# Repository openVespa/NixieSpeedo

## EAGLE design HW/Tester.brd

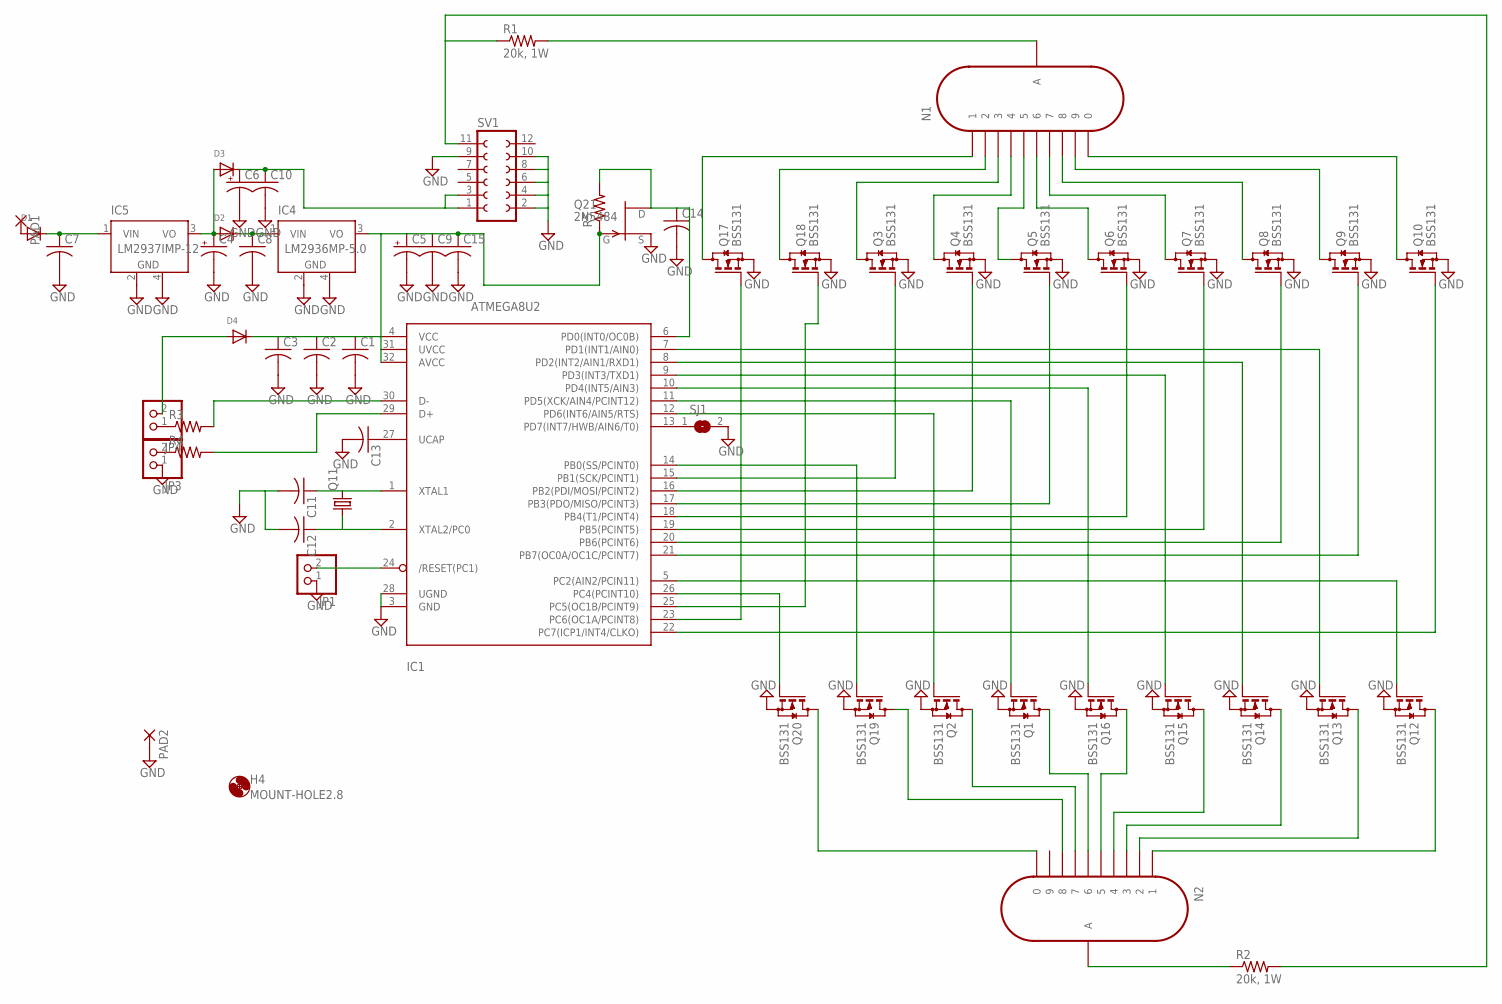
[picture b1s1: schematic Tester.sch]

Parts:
C1, C2, C3: C-USC0603K; C0603K
C4, C5, C6: CPOL-USE3.5-8; E3,5-8
C7, C8, C9, C10, C11, C12, C13, C14, C15: C-USC1206K; C1206K
D1, D2, D3: DIODESMA; SMADIODE
D4: DIODESOD-123; SOD-123
H4: MOUNT-HOLE2.8; 2,8
IC1: ATMEGA8U2; TQFP32-08
IC4: LM2936MP-5.0; SOT223
IC5: LM2937IMP-12; SOT223
JP1, JP3, JP4: PINHD-1X2; 1X02
N1, N2: IN-12A; IN-12
PAD1, PAD2: 3,81/1,4
Q1, Q2, Q3, Q4, Q5, Q6, Q7, Q8, Q9, Q10, Q12, Q13, Q14, Q15, Q16, Q17, Q18, Q19, Q20: BSS131; SOT23
Q11: CRYSTALHC49S; HC49/S
Q21: 2N5484; TO92-
R1: 20k, 1W; 0309/12
R2: 20k, 1W; 0309V
R3, R4, R5: R-US_R0805; R0805
SJ1: SJ
SV1: FE06-2

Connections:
GND: C1.2, C2.2, C3.2, C4.-, C5.-, C6.-, C7.2, C8.2, C9.2, C10.2, C11.2, C12.2, C13.2, C14.2, C15.2, IC1.3 (GND), IC1.28 (UGND), IC4.2 (GND), IC4.4 (GND), IC5.2 (GND), IC5.4 (GND), JP1.1, JP3.1, PAD2.1, Q1.2 (S), Q2.2 (S), Q3.2 (S), Q4.2 (S), Q5.2 (S), Q6.2 (S), Q7.2 (S), Q8.2 (S), Q9.2 (S), Q10.2 (S), Q12.2 (S), Q13.2 (S), Q14.2 (S), Q15.2 (S), Q16.2 (S), Q17.2 (S), Q18.2 (S), Q19.2 (S), Q20.2 (S), Q21.2 (S), SJ1.2, SV1.2, SV1.4, SV1.6, SV1.8, SV1.9, SV1.10
unnamed: IC1.15 (PB1(SCK/PCINT1)), Q3.1 (G)
unnamed: IC1.8 (PD2(INT2/AIN1/RXD1)), Q14.1 (G)
unnamed: IC1.9 (PD3(INT3/TXD1)), Q15.1 (G)
unnamed: IC1.10 (PD4(INT5/AIN3)), Q16.1 (G)
unnamed: IC1.16 (PB2(PDI/MOSI/PCINT2)), Q4.1 (G)
unnamed: IC1.17 (PB3(PDO/MISO/PCINT3)), Q5.1 (G)
unnamed: IC1.26 (PC4(PCINT10)), Q20.1 (G)
unnamed: IC1.14 (PB0(SS/PCINT0)), Q19.1 (G)
unnamed: IC1.12 (PD6(INT6/AIN5/RTS)), Q2.1 (G)
unnamed: IC1.11 (PD5(XCK/AIN4/PCINT12)), Q1.1 (G)
unnamed: IC1.5 (PC2(AIN2/PCIN11)), Q12.1 (G)
unnamed: IC1.18 (PB4(T1/PCINT4)), Q6.1 (G)
unnamed: IC1.19 (PB5(PCINT5)), Q7.1 (G)
unnamed: IC1.7 (PD1(INT1/AIN0)), Q13.1 (G)
unnamed: IC1.25 (PC5(OC1B/PCINT9)), Q18.1 (G)
unnamed: IC1.23 (PC6(OC1A/PCINT8)), Q17.1 (G)
unnamed: IC1.22 (PC7(ICP1/INT4/CLKO)), Q10.1 (G)
unnamed: IC1.21 (PB7(OC0A/OC1C/PCINT7)), Q9.1 (G)
unnamed: IC1.20 (PB6(PCINT6)), Q8.1 (G)
unnamed: C1.1, C2.1, C3.1, C5.+, C9.1, C15.1, D4.C, IC1.4 (VCC), IC1.31 (UVCC), IC1.32 (AVCC), IC4.3 (VO), Q21.1 (G), R5.1
unnamed: C7.1, D1.C, IC5.1 (VIN)
unnamed: C4.+, D2.A, D3.A, IC5.3 (VO)
unnamed: C8.1, D2.C, IC4.1 (VIN)
unnamed: C6.+, C10.1, D3.C, SV1.1, SV1.3
unnamed: C11.1, IC1.1 (XTAL1), Q11.2
unnamed: C12.1, IC1.2 (XTAL2/PC0), Q11.1
unnamed: D1.A, PAD1.1
unnamed: N1.1, Q17.3 (D)
unnamed: N1.2, Q18.3 (D)
unnamed: N1.3, Q3.3 (D)
unnamed: N1.4, Q4.3 (D)
unnamed: N1.5, Q5.3 (D)
unnamed: N1.0, Q10.3 (D)
unnamed: N1.9, Q9.3 (D)
unnamed: N1.8, Q8.3 (D)
unnamed: N1.7, Q7.3 (D)
unnamed: N1.6, Q6.3 (D)
unnamed: R1.1, R2.2, SV1.11
unnamed: JP3.2, R4.1
unnamed: N2.A, R2.1
unnamed: N2.0, Q20.3 (D)
unnamed: N2.1, Q12.3 (D)
unnamed: N2.2, Q13.3 (D)
unnamed: JP4.1, R3.1
unnamed: N2.3, Q14.3 (D)
unnamed: N2.4, Q15.3 (D)
unnamed: N2.5, Q16.3 (D)
unnamed: N2.6, Q1.3 (D)
unnamed: N2.7, Q2.3 (D)
unnamed: N2.8, Q19.3 (D)
unnamed: N1.A, R1.2
unnamed: IC1.24 (/RESET(PC1)), JP1.2
unnamed: IC1.29 (D+), R4.2
unnamed: D4.A, JP4.2
unnamed: C13.1, IC1.27 (UCAP)
unnamed: IC1.30 (D-), R3.2
unnamed: IC1.13 (PD7(INT7/HWB/AIN6/T0)), SJ1.1
unnamed: C14.1, IC1.6 (PD0(INT0/OC0B)), Q21.3 (D), R5.2

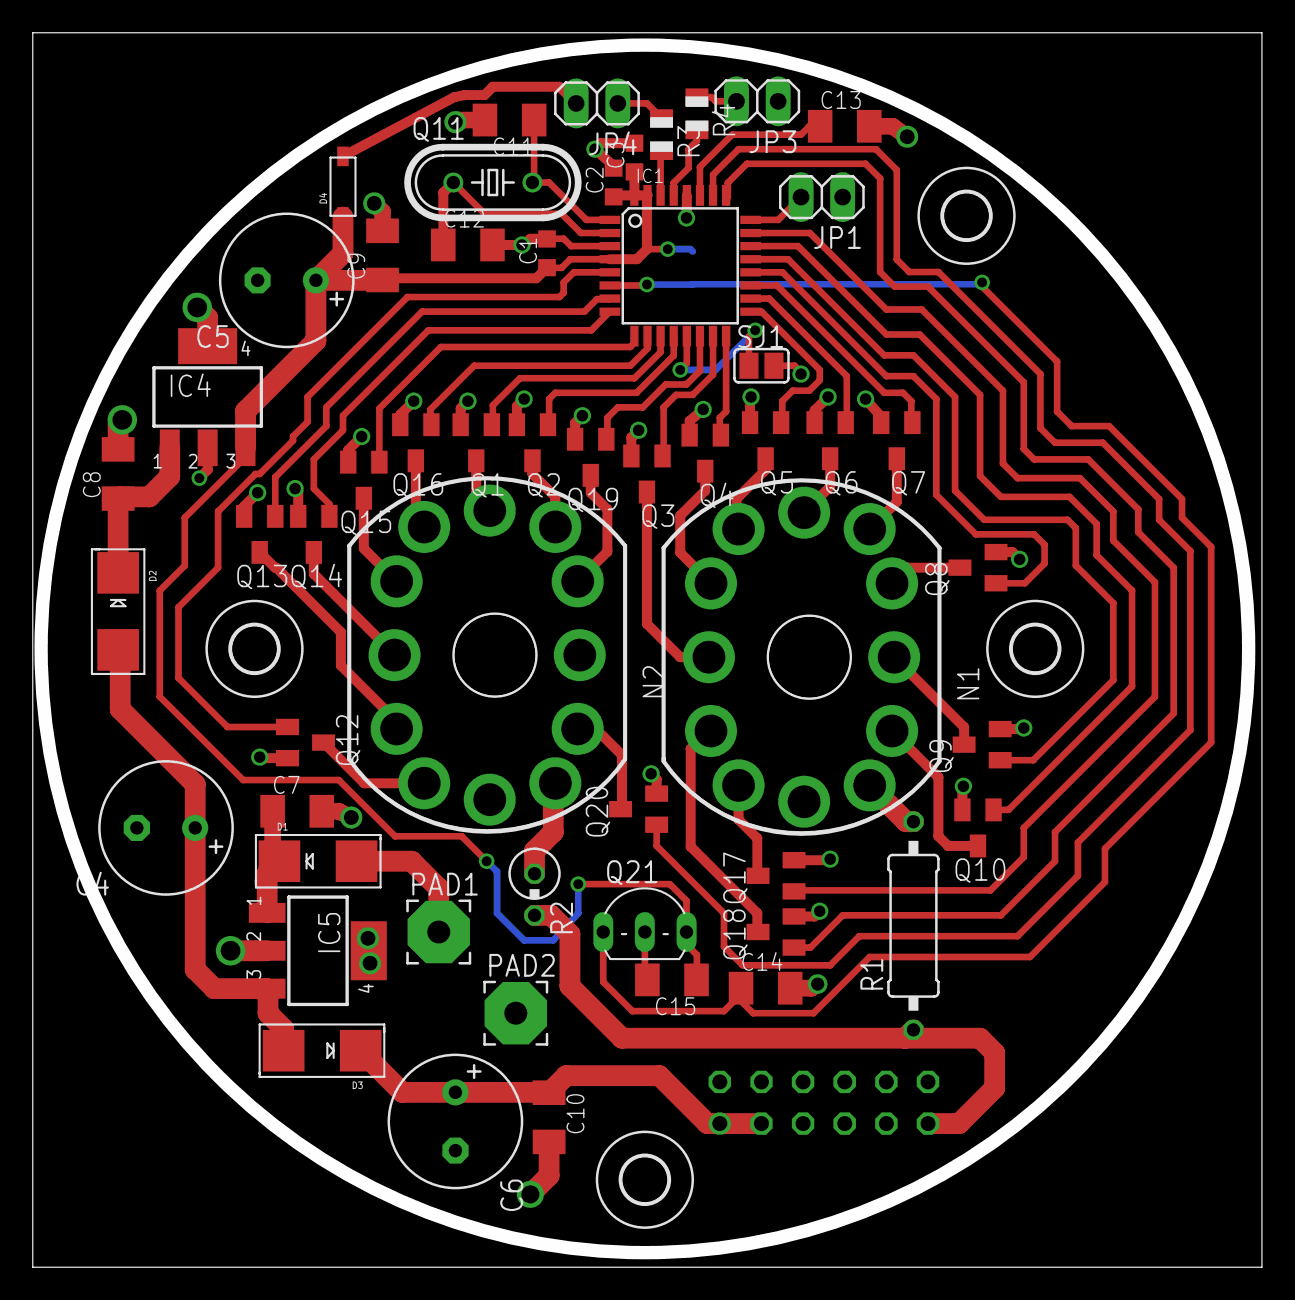
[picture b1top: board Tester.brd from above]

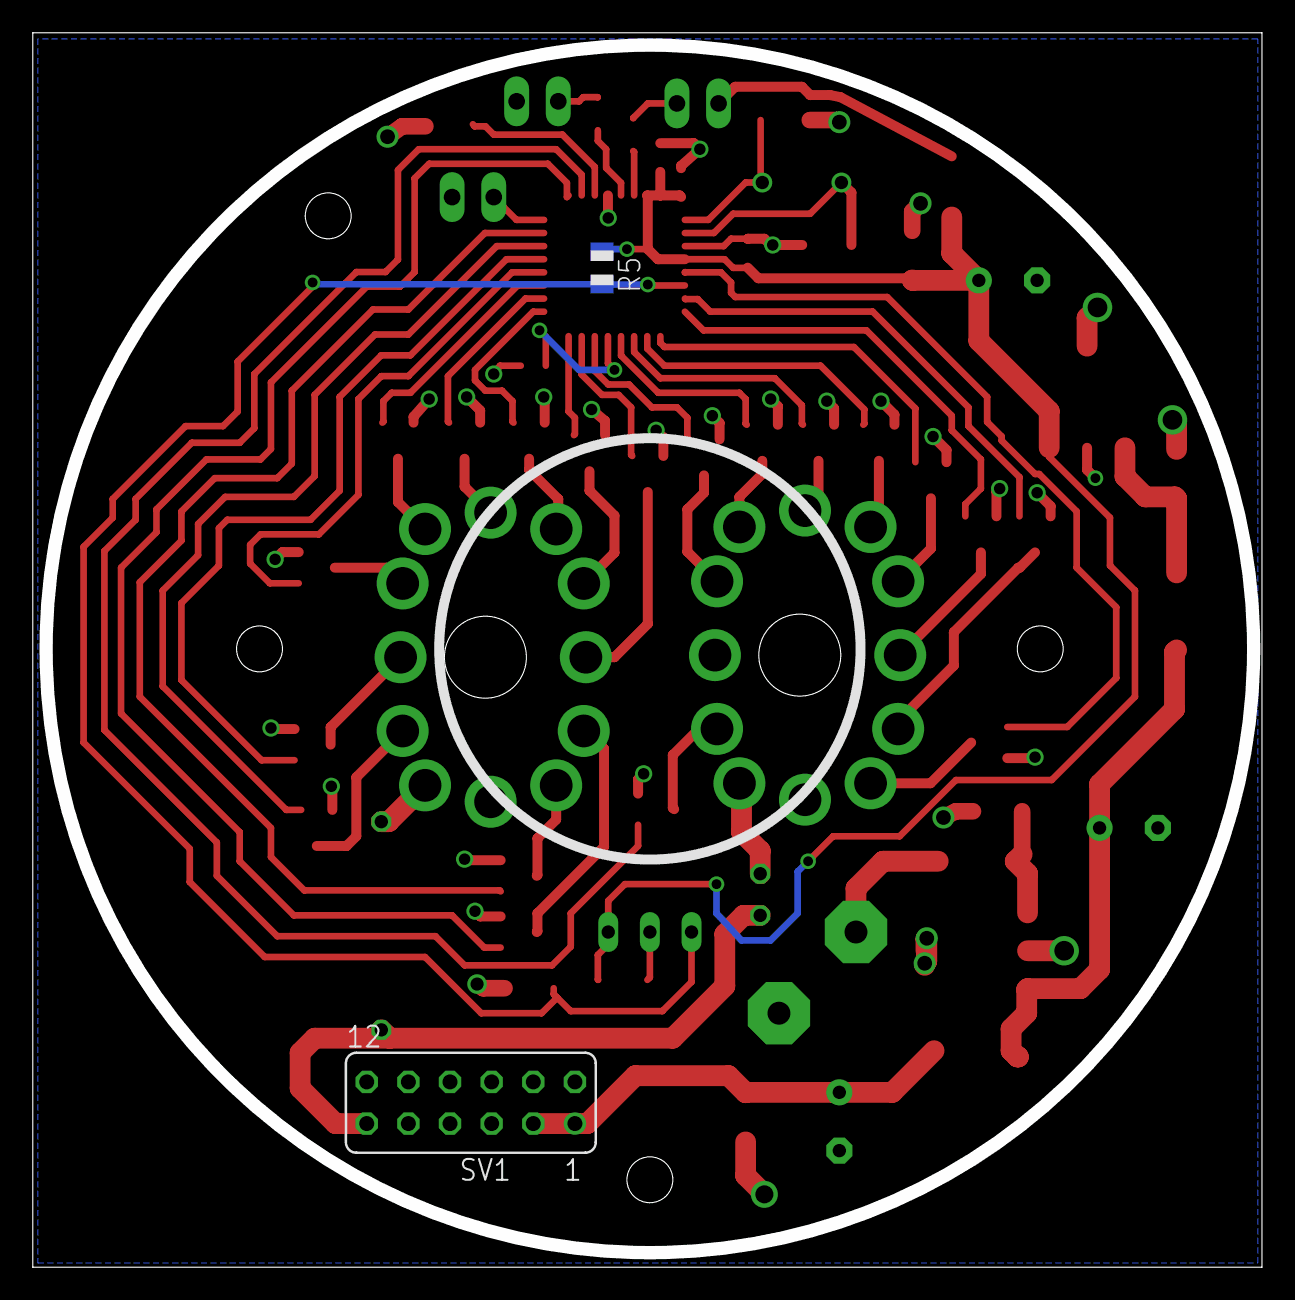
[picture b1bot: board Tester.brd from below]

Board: 2 copper layers, 74.2 x 74.5 mm, 61 parts (2 on the bottom side), 59 nets.

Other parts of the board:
H1, H2, H3: MOUNT-HOLE2.8; 2,8

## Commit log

2016-08-30 Create Temp
2016-08-30 Create Temp2
